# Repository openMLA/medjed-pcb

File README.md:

# Medjed Assembly

This repository contains the PCB files of the [MEDJED Maskless lithography system](https://github.com/openMLA/Medjed). PCB files are generated with KiCAD

Note that the [Wiki](https://github.com/openMLA/Medjed/wiki) and [Discussions](https://github.com/openMLA/Medjed/discussions) for the project are located in the main Medjed repository.

### Organisation

This repository should generally be obtained as a submodule of the main Medjed repository. That other repository will also have code and CAD files for the project.

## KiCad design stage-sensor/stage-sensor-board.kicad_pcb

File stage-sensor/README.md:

## Chuck Sensor PCB

This PCB is designed to fit into the sample chuck of the MEDJED system. It contains the following 3 sensors:

* A temperature and humidity sensor
* An accelerometer and gyroscope 
* A UV sensor

### UV sensor

The OPT3002 Light sensor will be useful to calibrate and correct for UV intensity of the illumination and projection system. The sensing area is smaller than the projected area, so some stage movement and averaging tricks will have to be applied. 

Some fiducial crosses and silkscreen markings have been added to help automation efforts and the finding of the IC when manually moving the stage around

### Temperature and Humidity sensor

The SHT45 temperature and humidity sensor is just for logging purposes. Changes in temperature and humidity can affect the photoresist and development process, so having a record of this is useful.

### Accelerometer and Gyroscope

The ICM42605 accelerometer and gyroscope unit can serve two purposes:

1. Get a feel for stage movement and apply input shaping to increase movement and settling speed (low priority)
2. Determine when the stage has settled and we are ready to expose an image.

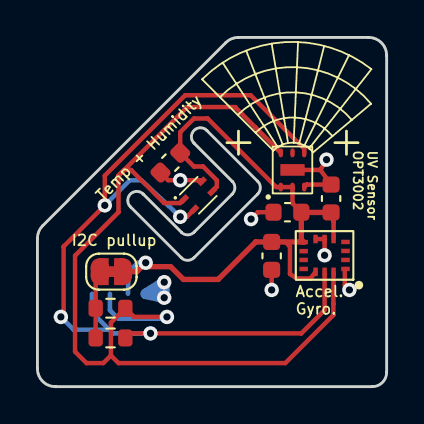
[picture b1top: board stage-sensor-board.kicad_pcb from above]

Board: 2 copper layers, 19.4 x 19.4 mm, 11 parts (1 on the bottom side), 5 nets.

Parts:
C3: 10nF; C_0603_1608Metric
C4: 2.2uF; C_0603_1608Metric
C5, C6: 100nF; C_0603_1608Metric
J1: STEMMA QT; JST_SH_SM04B-SRSS-TB_1x04-1MP_P1.00mm_Horizontal
JP1: Bridged; SolderJumper-2_P1.3mm_Bridged_RoundedPad1.0x1.5mm
R1, R2: 11K; R_0603_1608Metric
U1: ICM 42605; icm-42605
U2: OPT3002
U3: SHT45; SHT4X

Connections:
+3.3V: C3.1, C4.1, C5.2, C6.2, J1.2, JP1.2 (B), U1.5 (VDDIO), U1.8 (VDD), U1.12 (AP_CS), U2.1 (VDD), U2.2 (ADDR), U3.3 (VDD)
/I2C_pullup: JP1.1 (A), R1.1, R2.1
/SCL: J1.4, R2.2, U1.13 (SCL), U2.4 (SCL), U3.2 (SCL)
/SDA: J1.3, R1.2, U1.14 (SDA), U2.6 (SDA), U3.1 (SDA)
GND: C3.2, C4.2, C5.1, C6.1, J1.1, U1.1 (I2C_addr), U1.6 (GND), U1.7 (GND), U2.3 (GND), U3.4 (VSS)

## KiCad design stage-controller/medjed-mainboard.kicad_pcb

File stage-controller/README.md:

## Medjed Stage

The controller board for the Medjed stage is built around a Teensy 4.1, Snapmaker linear axes and external RLC2IC encoders. The signal of the encoders is processed and converted to step/dir signals for the snapmaker axes by Trinamic `TMC4631`

### I2C Connection

A STEMMA-QT connector (JST SH, 4 pin) is present on the board for any I2C peripherals. A planned connection would be a UV sensor to be fitted on the stage that will serve as stage calibration. 

### CAN Bus

The Snapmaker linear axes use a CAN bus to talk to the MCU inside the axes (reporting on endstop status and such). It would be quite inefficient to put a CAN transceiver for each of the axes, but running them as part of a single CAN bus means we need to go slightly outside of recommended CAN bus parameters. 

The cables for the linear axes are 40cm, and I assume that the transmission line is terminated with 120Ohm impedance. Running three terminated nodes may prove to be too much for the transceiver to power. In addition, the 40cm cable length is a little over the recommended max length for CAN nodes. I think both concerns are not fundamentally unworkable. The bus speed may need to be reduced to compensate, but this shouldn't really be an issue for the targeted application.

> Future designs should probably expose a CAN bus for other peripherals to be connected; or to handle communication with devices on the Z-axi.

### Safety

The Emergency Stop (`ESTOP`) signal is controllable from the teensy, but features manual trigger in the form of a simple PCB switch and a terminal for external switches. 

> Future revisions will need a proper EMO switch that kills power to all systems (axes and optics)

### Power considerations

The snapmaker linear axes use 24V supply. The snapmaker power supply comes with plenty of overhead in terms of power (as it need to be able to run a 3D printer heated bed) so that is not a concern. 

We also need 5V and 3.3V supply on the board.

5V:

* Teensy 4.1: 100mA
* [3X] RLC2IC encoders: <30mA (no termination resistors) or <130mA with 120ohm termination.

3.3V:

* TMC4631: ???

1.8V:

* TMC4631: ???

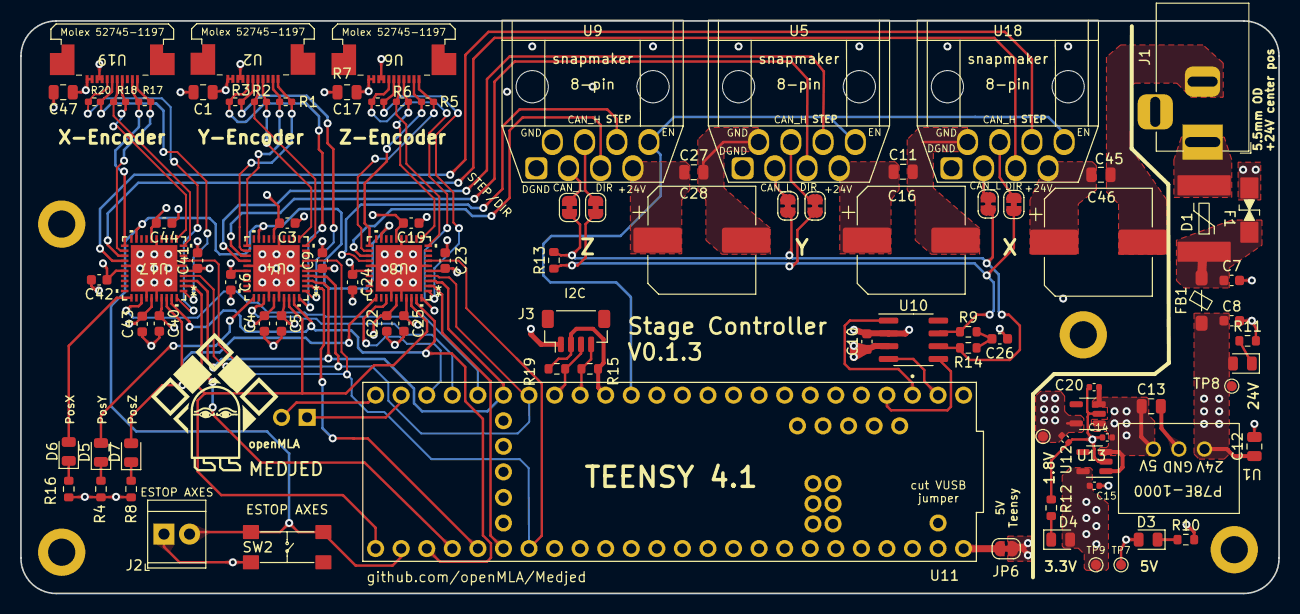
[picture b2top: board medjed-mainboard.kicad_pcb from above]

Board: 4 copper layers, 125.0 x 56.9 mm, 93 parts (0 on the bottom side), 71 nets.

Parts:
C1, C11, C12, C17, C27, C45, C47: 10uF; C_0805_2012Metric
C3, C4, C5, C6, C7, C8, C9, C10, C19, C22, C23, C24, C25, C40, C41, C42, C43, C44: 100nF; C_0603_1608Metric
C13: 22uF; C_0805_2012Metric
C14, C15, C20, C21: 1uF; C_0402_1005Metric
C16, C28, C46: 220uF; CP_Elec_220uf
C26: 4.7nF; C_0603_1608Metric
D1: SMAJ28CA
D2, D3, D4, D5, D6, D7: Red; LED_0805_2012Metric
F1: SMDC185F/33-2; SMDC185F_33-2
FB1: FerriteBead; BLM41P600S
J1: Barrel_Jack; BarrelJack_Horizontal
J2: ESTOP terminal; TerminalBlock_TE_282834-2_1x02_P2.54mm_Horizontal
J3: Stemma QT; JST_SH_BM04B-SRSS-TB_1x04-1MP_P1.00mm_Vertical
J4: GPIO; PinSocket_1x02_P2.54mm_Vertical
JP1, JP2, JP3, JP4, JP5, JP6, JP7: SolderJumper_2_Bridged; SolderJumper-2_P1.3mm_Bridged_RoundedPad1.0x1.5mm
R1, R2, R3, R5, R6, R7, R17, R18, R20: 120; R_0402_1005Metric_Pad0.72x0.64mm_HandSolder
R4, R8, R10, R11, R12, R15, R16, R19: 5k1; R_0603_1608Metric
R9, R14: 60.4; R_0603_1608Metric
R13: 120; R_0603_1608Metric
SW2: ESTOP switch; E-switch-button
TP7, TP8, TP9, TP10: TestPoint; TestPoint_Pad_D1.0mm
U1: P78E-1000
U2, U6, U19: Molex 52745-1197
U4, U8, U17: TMC4361A-LA; TMC4361A_QFN40_6X6_TRI
U5, U9, U18: snapmaker_8-pin
U10: TCAN330; SOIC-8_3.9x4.9mm_P1.27mm
U11: teensy 4.1; teensy_4.1
U12: MIC5317-3.3; SOT-23-5
U13: MIC5317-1.8; SOT-23-5

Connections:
+1V8: C3.2, C4.2, C19.2, C21.1, C22.2, C43.2, C44.2, TP10.1, U4.16 (VDD1V8), U4.35 (VDD1V8), U8.16 (VDD1V8), U8.35 (VDD1V8), U13.5 (Vout), U17.16 (VDD1V8), U17.35 (VDD1V8)
+3.3V: C5.1, C6.1, C9.1, C10.1, C15.1, C23.1, C24.1, C25.1, C40.1, C41.1, C42.1, D4.2 (A), TP9.1, U4.5 (VCC), U4.26 (VCC), U4.37 (VCC), U8.5 (VCC), U8.26 (VCC), U8.37 (VCC), U10.3 (VCC), U12.5 (Vout), U17.5 (VCC), U17.26 (VCC), U17.37 (VCC)
+5V: C1.1, C13.1, C14.1, C17.1, C20.1, C47.1, D3.2 (A), JP6.2 (B), TP7.1, U1.3 (Vout), U2.1 (+5V), U2.2 (+5V), U6.1 (+5V), U6.2 (+5V), U12.1 (Vin), U12.3 (EN), U13.1 (Vin), U13.3 (EN), U19.1 (+5V), U19.2 (+5V)
+24V: C8.1, C11.1, C12.1, C16.1, C27.1, C28.1, C45.1, C46.1, D2.2 (A), FB1.2, TP8.1, U1.1 (Vin), U5.7 (+24V), U9.7 (+24V), U18.7 (+24V)
/+3.3V Teensy: J3.2, R15.1, R19.1, U11.3.3V_1 (3.3V), U11.3.3V_2 (3.3V), U11.3.3V_3 (3.3V)
/+24Vfused: C7.1, D1.2 (A2), F1.2, FB1.1
/+24Vsrc: F1.1, J1.1
/Axis X/A+: R20.2, U17.40 (A), U19.5 (A+)
/Axis X/A-: R20.1, U17.1 (A-), U19.6 (A-)
/Axis X/B+: R18.2, U17.10 (B), U19.7 (B+)
/Axis X/B-: R18.1, U17.11 (B-), U19.8 (B-)
/Axis X/CAN_H: JP5.1 (A), U18.4 (CAN_H)
/Axis X/CAN_L: JP7.1 (A), U18.3 (CAN_L)
/Axis X/DIR: U17.23 (DIROUT_PWMB), U18.5 (DIR)
/Axis X/STEP: U17.24 (STPOUT_PWMA), U18.6 (STEP)
/Axis X/TGT: D6.2 (A), U17.31 (TARGET_REACHED)
/Axis X/Z+: R17.2, U17.21 (N), U19.10 (Z+)
/Axis X/Z-: R17.1, U17.22 (N-), U19.11 (Z-)
/Axis Y/A+: R3.2, U2.5 (A+), U4.40 (A)
/Axis Y/A-: R3.1, U2.6 (A-), U4.1 (A-)
/Axis Y/B+: R2.2, U2.7 (B+), U4.10 (B)
/Axis Y/B-: R2.1, U2.8 (B-), U4.11 (B-)
/Axis Y/CAN_H: JP4.1 (A), U5.4 (CAN_H)
/Axis Y/CAN_L: JP3.1 (A), U5.3 (CAN_L)
/Axis Y/DIR: U4.23 (DIROUT_PWMB), U5.5 (DIR)
/Axis Y/STEP: U4.24 (STPOUT_PWMA), U5.6 (STEP)
/Axis Y/TGT: D5.2 (A), U4.31 (TARGET_REACHED)
/Axis Y/Z+: R1.2, U2.10 (Z+), U4.21 (N)
/Axis Y/Z-: R1.1, U2.11 (Z-), U4.22 (N-)
/Axis Z/A+: R7.2, U6.5 (A+), U8.40 (A)
/Axis Z/A-: R7.1, U6.6 (A-), U8.1 (A-)
/Axis Z/B+: R6.2, U6.7 (B+), U8.10 (B)
/Axis Z/B-: R6.1, U6.8 (B-), U8.11 (B-)
/Axis Z/CAN_H: JP1.1 (A), U9.4 (CAN_H)
/Axis Z/CAN_L: JP2.1 (A), U9.3 (CAN_L)
/Axis Z/DIR: U8.23 (DIROUT_PWMB), U9.5 (DIR)
/Axis Z/STEP: U8.24 (STPOUT_PWMA), U9.6 (STEP)
/Axis Z/TGT: D7.2 (A), U8.31 (TARGET_REACHED)
/Axis Z/Z+: R5.2, U6.10 (Z+), U8.21 (N)
/Axis Z/Z-: R5.1, U6.11 (Z-), U8.22 (N-)
/SCL: J3.4, R15.2, U11.24 (A10)
/SDA: J3.3, R19.2, U11.25 (A11)
CAN_EN: U10.5 (SHDN), U11.2 (OUT2)
CAN_H: JP1.2 (B), JP4.2 (B), JP5.2 (B), R9.1, R13.1, U10.7 (CANH)
CAN_L: JP2.2 (B), JP3.2 (B), JP7.2 (B), R13.2, R14.2, U10.6 (CANL)
CS_X: U11.36 (CS2), U17.2 (NSCSIN)
CS_Y: U4.2 (NSCSIN), U11.37 (CS3)
CS_Z: U8.2 (NSCSIN), U11.38 (A14)
EN_SNAP: U5.8 (EN), U9.8 (EN), U11.12 (MISO), U18.8 (EN)
ESTOP: J2.2, SW2.3 (K), SW2.4 (A), U4.19 (NFREEZE), U8.19 (NFREEZE), U11.34 (RX8), U17.19 (NFREEZE)
GND: C1.2, C3.1, C4.1, C5.2, C6.2, C7.2, C8.2, C9.2, C10.2, C11.2, C12.2, C13.2, C14.2, C15.2, C16.2, C17.2, C19.1, C20.2, C21.2, C22.1, C23.2, C24.2, C25.2, C26.1, C27.2, C28.2, C40.2, C41.2, C42.2, C43.1, C44.1, C45.2, C46.2, C47.2, D1.1 (A1), J1.2, J2.1, J3.1, R4.2, R8.2, R10.2, R11.2, R12.2, R16.2, SW2.1, U1.2 (GND), U2.3 (GND), U2.4 (GND), U4.6 (GND), U4.15 (GND), U4.25 (GND), U4.34 (TEST_MODE), U4.36 (GND), U4.41 (GND), U5.1 (DGND), U5.2 (GND), U6.3 (GND), U6.4 (GND), U8.6 (GND), U8.15 (GND), U8.25 (GND), U8.34 (TEST_MODE), U8.36 (GND), U8.41 (GND), U9.1 (DGND), U9.2 (GND), U10.2 (GND), U11.GND1 (GND), U11.GND2 (GND), U11.GND3 (GND), U11.GND4 (GND), U11.GND5 (GND), U12.2 (GND), U13.2 (GND), U17.6 (GND), U17.15 (GND), U17.25 (GND), U17.34 (TEST_MODE), U17.36 (GND), U17.41 (GND), U18.1 (DGND), U18.2 (GND), U19.3 (GND), U19.4 (GND)
INT_X: U11.28 (RX7), U17.33 (INTR)
INT_Y: U4.33 (INTR), U11.29 (TX7)
INT_Z: U8.33 (INTR), U11.30 (CRX3)
MISO: U4.7 (SDOIN), U8.7 (SDOIN), U11.39 (A15), U17.7 (SDOIN)
MOSI: U4.4 (SDIIN), U8.4 (SDIIN), U11.26 (A12), U17.4 (SDIIN)
unnamed: C26.2, R9.2, R14.1
unnamed: D2.1 (K), R11.1
unnamed: D3.1 (K), R10.1
unnamed: D4.1 (K), R12.1
unnamed: D5.1 (K), R4.1
unnamed: D6.1 (K), R16.1
unnamed: D7.1 (K), R8.1
unnamed: JP6.1 (A), U11.VIN
unnamed: U10.4 (RXD), U11.0 (RX1)
unnamed: U10.1 (TXD), U11.1 (TX1)
Pin 1: J4.1, U11.31 (CTX3)
Pin 2: J4.2, U11.32 (OUT1B)
RST_AXES: U4.39 (NRST), U8.39 (NRST), U11.35 (TX8), U17.39 (NRST)
SCK: U4.3 (SCKIN), U8.3 (SCKIN), U11.27 (A13), U17.3 (SCKIN)
TeensyCLK: U4.38 (CLK_EXT), U8.38 (CLK_EXT), U11.33 (MCLK2), U17.38 (CLK_EXT)

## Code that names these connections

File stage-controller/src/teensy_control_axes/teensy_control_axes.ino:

// written for use on Teensy 4.1
#include <SPI.h>  // include the SPI library:

const int CS_X = 36;
const int CS_Y = 37;
const int CS_Z = 38;
const int clkPin = 33;

void setup() {
  Serial.println("\n\nSetting up the TMC4361 axes...\n\n");

  // set the slaveSelectPin as an output:
  pinMode (CS_X, OUTPUT);
  pinMode (CS_Y, OUTPUT);
  pinMode (CS_Z, OUTPUT);

  digitalWrite(CS_X,HIGH);  // make sure X axis is OFF
  digitalWrite(CS_Y,HIGH);  // make sure Y axis is OFF
  digitalWrite(CS_Z,HIGH);  // make sure Z axis is OFF

  int32_t ext_clock_freq = 18750000;
  analogWriteFrequency(clkPin, ext_clock_freq);  // try to get 18.75MHz clock signal out for TMC4361
  analogWrite(clkPin, 128);
  Serial.println("External clock signal for TMC4631 set...");

  delay(500);  // wait a bit for the TMC4361 to figure itself out.

  SPISettings spi_settings(2000000, MSBFIRST, SPI_MODE3); 

  // initialize SPI:
  SPI1.setMISO(39);
  SPI1.begin(); 
  SPI1.setMISO(39);
  SPI1.beginTransaction(spi_settings);
  Serial.println("\n\nSPI hardware initialised...\n\n");
  
  check_SPI(CS_X);
  check_SPI(CS_Y);
  check_SPI(CS_Z);

  int CS_ACTIVE = CS_X;

  // set up motion axis X
  configure_axis(CS_ACTIVE);

  // write nonzero target position
  // byte target_data[] = {0x37, 0b00000000, 0x00, 0x04, 0xFF};  // signed 32 bit (so max 2^31)
  // write_spi(CS_ACTIVE, target_data);
  set_position(CS_ACTIVE, 1200);

  for (int i = 1; i < 10; i++) {
    print_position(CS_ACTIVE);
    delay(200);
  }

  // write nonzero target position (warning: stage moves)
  set_position(CS_ACTIVE, -1400);

  for (int i = 1; i < 40; i++) {
    print_position(CS_ACTIVE);
    delay(200);
  }
}

void loop() {
  
  delay(5000);
}

void configure_axis(int CS_pin) {
  /// Set up axis to the point where the move commands can be called

  // Set up the correct external clock speed
  // important to have velocity be in "physically accurate" steps/time 
  write_spi(CS_pin, 0x31, 0x11E11A30);  // see ext_clock_freq. Claimed to be 24:0 but that cannot be right? doesnt fit values

  // zero position position and target
  write_spi(CS_pin, 0x21, 0);  // position
  write_spi(CS_pin, 0x37, 0);  // target

  // extend the pulsewidth for the step/dir signals
  write_spi(CS_pin, 0x10, 0x00000000 + 0b00001111);  // set STEP duration to be 15 clock cycles, instead of just 1 

  // write ramp mode
  write_spi(CS_pin, 0x20, 0x00000000 + 0b00000101); // POSITION mode, with trapezoidal ramp

  // set max acceleration/deceleration
  write_spi(CS_pin, 0x28, 0x0000FFFF); // 23:0 are relevant
  write_spi(CS_pin, 0x29, 0x0000FFFF);

  // set max velocity
  write_spi(CS_pin, 0x24, 0x0002FF00); // 31:0 are relevant, 23 digits, 8 decimal places

  delay(200);  // can be removed, but means the POS=TARGET led will be lit for a bit
}

signed long get_position(int CS_pin) {
  return read_spi(CS_pin, 0x21);
}

void print_position(int CS_pin) {
  Serial.printf("Position is: %ld\n", get_position(CS_pin));
  Serial.printf("Position is: %x\n", get_position(CS_pin));
}

void set_position(int CS_pin, signed long position) {
  Serial.printf("> Moving axis %d to position %ld...\n",  CS_pin, position);
  write_spi(CS_pin, 0x37, position);
}

void check_SPI(int CS_pin) {
  /// checks if the TMC4361 at the CS_pin is giving the expected response.
  /// 
  /// It is recommend that you call this function before any SPI communication as the first response
  /// over SPI is nonsense or something. Anyway, this should make sure SPI is ready and working before
  /// you start going serious work over that serial interface.

  unsigned long response = read_spi(CS_pin, 0x00);  // read the general register (0x00)
  
  if (response == 0x00006020) {
    printf("SPI communication with CS %d is OK!\n", CS_pin);
  } else {
    printf("Did not get expected response over SPI for CS %d\n", CS_pin);
  }
}

unsigned long read_spi(int CS_pin, byte spi_register) {
  // first we must write the register we want to read
  digitalWrite(CS_pin,LOW);  

  SPI1.transfer(spi_register);
  for (int i = 1; i < 5; i++) {
    SPI1.transfer(0x00);
  } 

  // take the SS pin high to de-select the chip:
  digitalWrite(CS_pin,HIGH); 

  // and now we can read out the actual values. We send the same query, but we could pick any valid register.
  return read_spi_single(CS_pin, spi_register);
}

unsigned long read_spi_single(int CS_pin, byte spi_register) {

  unsigned long response;

  digitalWrite(CS_pin,LOW);  
  delayMicroseconds(10);

  SPI1.transfer(spi_register);
  for (int i = 1; i < 4; i++) {
    response |= SPI1.transfer(0x00);
    //Serial.printf("got response (same cycle): %x\n", response);
    response <<= 8;
  } 
  response |= SPI1.transfer(0x00);  // dont need a bit shift after last byte

  // take the SS pin high to de-select the chip:
  digitalWrite(CS_pin,HIGH);

  return response;
}

void write_spi(int CS_pin, byte address, unsigned long data) {
  //TMC4361 takes 5-byte bit data: 8 address and 32 data

  //Serial.printf("\nWriting SPI data %x to register %x\n", data, address);

  digitalWrite(CS_pin,LOW);
  delayMicroseconds(10);

  // to send write request we add 0b10000000 to the equivalent read address
  SPI1.transfer(address + 0x80);  // address
  SPI1.transfer((data >> 24) & 0xff);
  SPI1.transfer((data >> 16) & 0xff);
  SPI1.transfer((data >> 8) & 0xff);
  SPI1.transfer((data) & 0xff);
  digitalWrite(CS_pin,HIGH);

  // and we read back the value to check that it was set correctly
  unsigned long readback = read_spi_single(CS_pin, address);

  // compare values
  if (readback != data) {
    Serial.printf("> SPI write mismatch: read %x but expected %x \n", readback, data);
  }
}

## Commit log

2023-10-29 Intial commit after splitting into separate repository
    Used to be part of Medjed, but after reorganisation it will be a separate repository. History is still avaialable in archived version of medjed repository. Check out Medjed repository for more inform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
2023-10-29 Update schematic preview jpg
2023-10-30 Remove affinity designer file
    File should not have been committed
2023-10-30 update gitignore
2024-02-10 fix silkscreen error
    Silkscreen labelled the 1.8V net as 1.5V, which is confusing. Fixed by editing the silkscreen label.
2024-02-10 fix references to old IC in readme
2024-02-13 fix Teensy 4.1 footprint
    Original footprint had through hole pads that were too small (0.8mm diameter). New ones are bigger to accomodate common pin headers.
2024-04-27 Fix Clock pin and MISO/MOSI error
    The TeensyCLK signal was routed to a pin on the Teensy 4.1 that did not support PWM. Now fixed. MOSI and MISO of SPI interface were flipped around by mistake. Now in correct orientation and should al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
2024-04-27 Add basic stage code for teensy
    Simple code with a few basic abstractions. Still needs a good homing procedure and does not use the encoder interface.
2024-04-28 Removed differential line receivers
    During design of the board I did not realise that the TMC4631 already has this built in (I had different motion controllers before). So the AM26LS32A ICs should not be needed. Removed these and rerou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
2024-04-28 fix broken image
    Capitalisation of JPG doesnt work in GitHub
2024-05-15 Stage sensor board V0.1.1
    Switched out the vertical stemma QT for horizontal one. Funciontally equivalent to V0.1.1 WIll send this one over for production.
